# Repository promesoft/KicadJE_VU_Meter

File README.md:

# KicadJE_VU_Meter
Faceplate for 35mm VU Meter

# Purpose

## Board 1
Adjustment:

Input Audio 
+/- 10V DC coupled

Output Audio  
+/- 10V DC coupled

# Status - Delivered
## Initial 
| Stage  | Detail | Status |
| ------------- | ------------- | ------------- |
| create material  | sch |OK
| | pcb |OK
| | gerber |OK
| production |  |  
|  | produced  |OK 
|  | delivered |OK
## Preliminary validation
| Test  | Detail | Status |
| ------------- | ------------- | ------------- |
| Initial Inspection | | ok |
| Mechanical Inspection | | 6,3mm jack on the small side |
| Initial Technical Test | Board 1 |  |
| Initial Product Test | Board1 |  |

## Secondary validation
| Test  | Detail | Status |
| ------------- | ------------- |------------- |
| Product Test | 1 | |
| Quality | 1 | |
| Long Term Product Test |  |  |
| Power Draw |  | 

## Errata
### Errata - 

## Issues and Notes
### 

# Pictures

# Schematic
## Sch 1

# Analysis
## Diag 1

## Prototype

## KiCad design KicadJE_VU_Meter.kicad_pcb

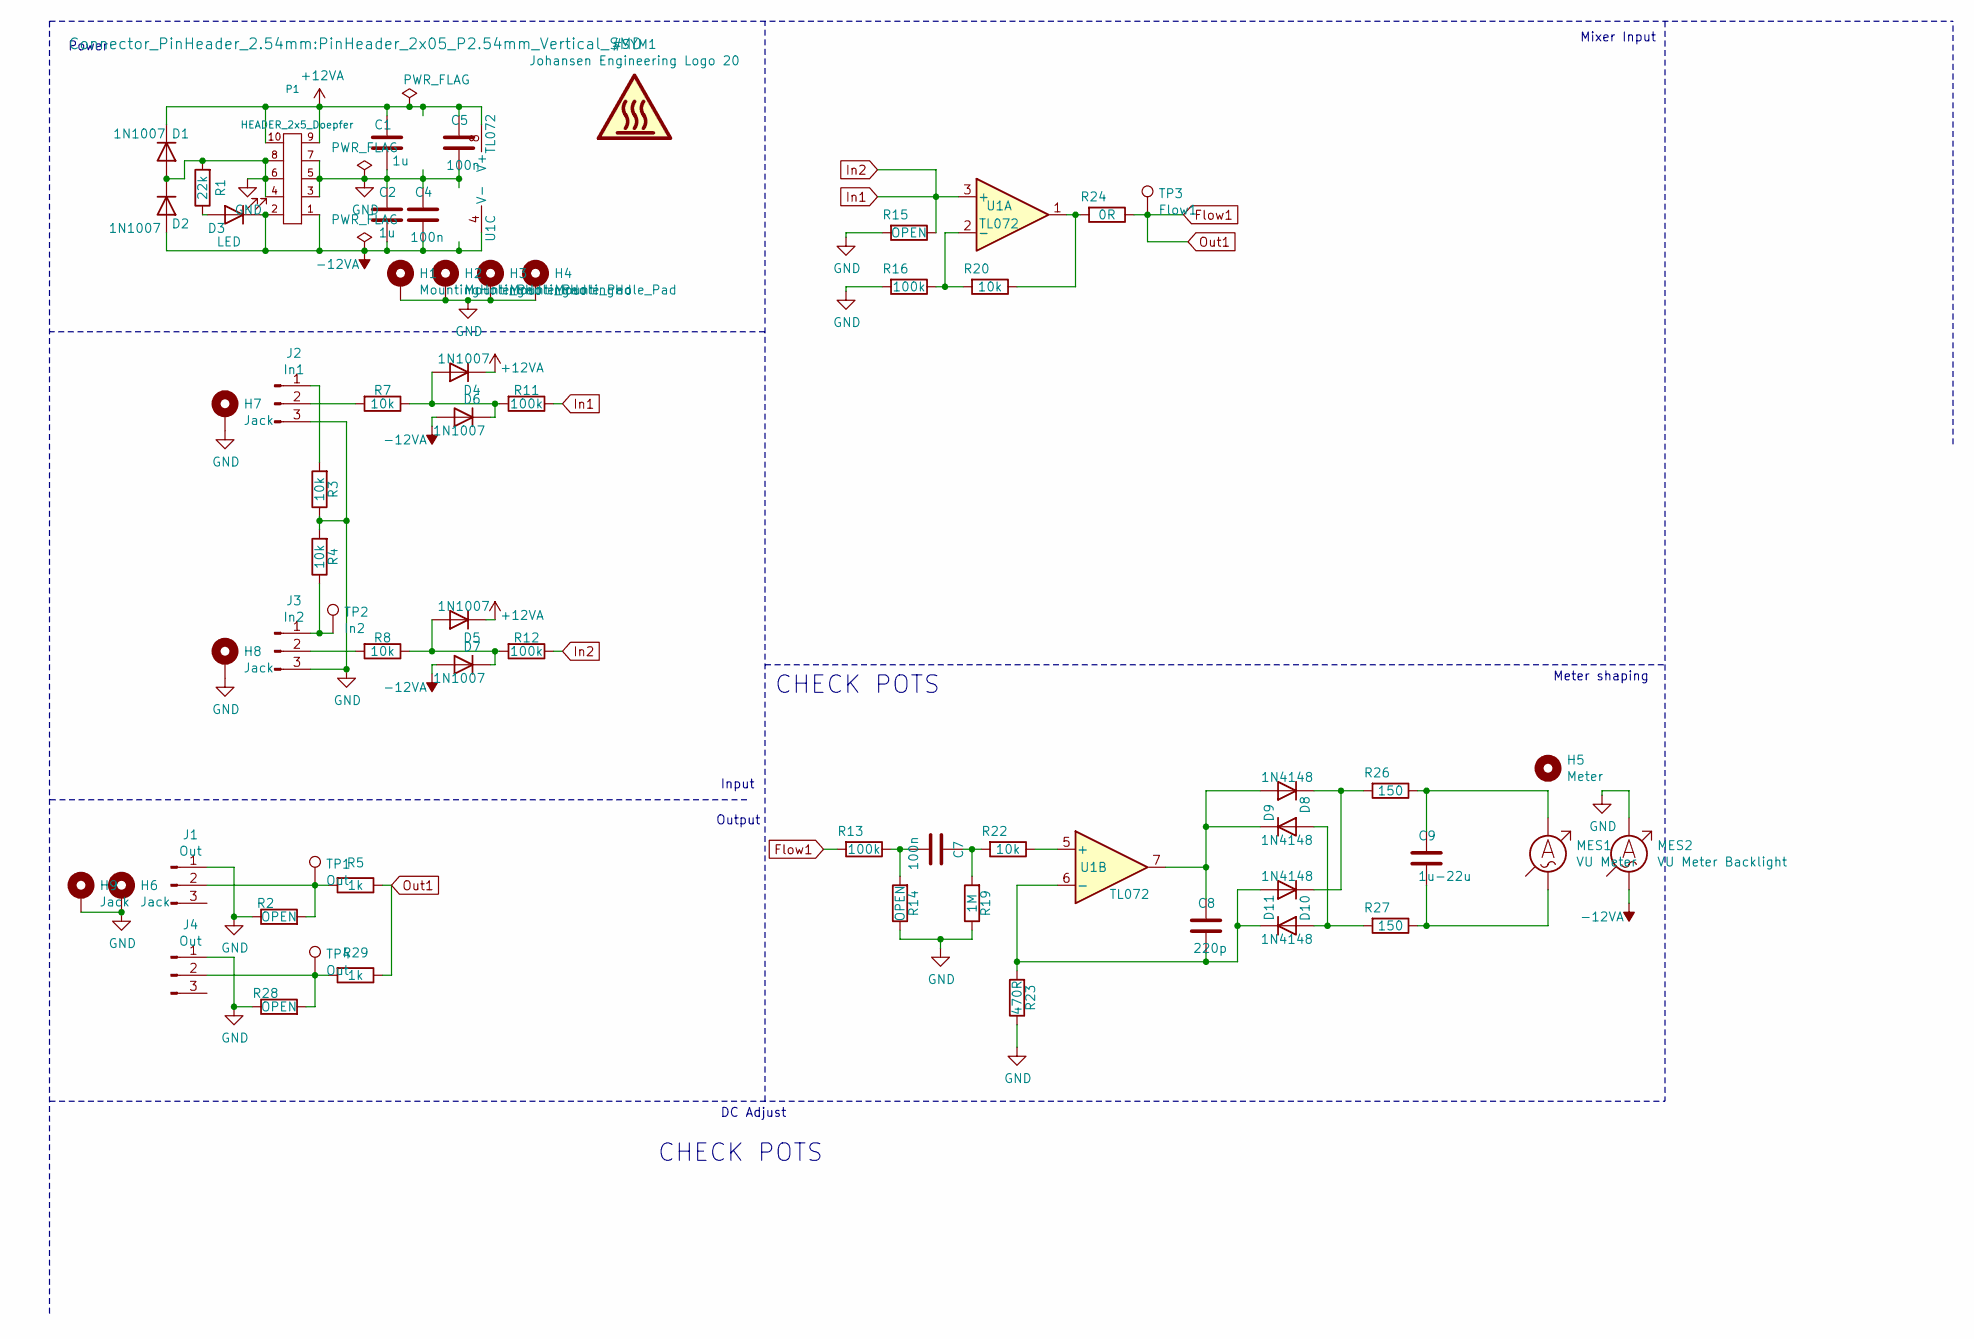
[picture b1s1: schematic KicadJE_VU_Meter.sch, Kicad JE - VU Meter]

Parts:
C1, C2: 1u; C_0805_2012Metric
C4, C5, C7: 100n; C_0805_2012Metric
C8: 220p; C_0805_2012Metric
C9: 1u-22u; C_1206_3216Metric
D1, D2, D4, D5, D6, D7: 1N1007; D_SOD-123
D3: LED; LED_0805_2012Metric_Pad1.15x1.40mm_HandSolder
D8, D9, D10, D11: 1N4148; D_MiniMELF
H1, H2, H3, H4: MountingHole_Pad; MountingHole_Eurorack3
H5: Meter; VU_Meter_Hole
H6: Jack; Jack_6m3
H7, H8, H9: Jack; Jack_3m5
J1, J4: Out; PinHeader_1x03_P2.54mm_Vertical_SMD_Pin1Right
J2: In1; PinHeader_1x03_P2.54mm_Vertical_SMD_Pin1Right
J3: In2; PinHeader_1x03_P2.54mm_Vertical_SMD_Pin1Right
MES1: VU Meter; PinHeader_1x02_P2.54mm_Vertical_SMD_Pin1Right
MES2: VU Meter Backlight; PinHeader_1x02_P2.54mm_Vertical_SMD_Pin1Right
P1: HEADER_2x5_Doepfer; PinHeader_2x05_P2.54mm_Vertical_SMD
R1: 22k; R_0805_2012Metric_Pad1.20x1.40mm_HandSolder
R2, R14, R15, R28: OPEN; R_0805_2012Metric_Pad1.20x1.40mm_HandSolder
R3, R4, R7, R8, R20, R22: 10k; R_0805_2012Metric_Pad1.20x1.40mm_HandSolder
R5, R29: 1k; R_0805_2012Metric_Pad1.20x1.40mm_HandSolder
R11, R12, R13, R16: 100k; R_0805_2012Metric_Pad1.20x1.40mm_HandSolder
R19: 1M; R_0805_2012Metric_Pad1.20x1.40mm_HandSolder
R23: 470R; R_0805_2012Metric_Pad1.20x1.40mm_HandSolder
R24: 0R; R_0805_2012Metric_Pad1.20x1.40mm_HandSolder
R26, R27: 150; R_0805_2012Metric_Pad1.20x1.40mm_HandSolder
TP1, TP4: Out; TestPoint_Pad_D2.0mm
TP2: In2; TestPoint_Pad_D2.0mm
TP3: Flow1; TestPoint_Pad_D2.0mm
U1: TL072; SO-8_5.3x6.2mm_P1.27mm

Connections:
+12VA: C1.1, C5.1, D1.1 (K), D4.1 (K), D5.1 (K), P1.9 (+12), P1.10 (+12), U1.8 (V+)
-12VA: C2.2, C4.2, D2.2 (A), D3.1 (K), D6.2 (A), D7.2 (A), MES2.1, P1.1 (-12), P1.2 (-12), U1.4 (V-)
Flow1: R5.1, R13.2, R24.1, R29.1, TP3.1
GND: C1.2, C2.1, C4.1, C5.2, D1.2 (A), D2.1 (K), H1.1, H2.1, H3.1, H4.1, H6.1, H7.1, H8.1, H9.1, J1.1, J2.3, J3.3, J4.1, MES2.2, P1.3 (GND), P1.4 (GND), P1.5 (GND), P1.6 (GND), P1.7 (GND), P1.8 (GND), R1.2, R2.1, R3.1, R4.2, R14.1, R15.2, R16.2, R19.1, R23.1, R28.1
In1: R11.1, R12.1, R15.1, U1.3 (+)
unnamed: C7.1, R19.2, R22.2
unnamed: C7.2, R13.1, R14.2
unnamed: C8.1, D8.2 (A), D9.1 (K), U1.7
unnamed: C8.2, D10.2 (A), D11.1 (K), R23.2, U1.6 (-)
unnamed: C9.1, MES1.2, R26.1
unnamed: C9.2, MES1.1, R27.1
unnamed: D3.2 (A), R1.1
unnamed: D4.2 (A), D6.1 (K), R7.1, R11.2
unnamed: D5.2 (A), D7.1 (K), R8.1, R12.2
unnamed: D8.1 (K), D10.1 (K), R26.2
unnamed: D9.2 (A), D11.2 (A), R27.2
unnamed: J1.2, R2.2, R5.2, TP1.1
unnamed: J2.1, R3.2
unnamed: J2.2, R7.2
unnamed: J3.1, R4.1, TP2.1
unnamed: J3.2, R8.2
unnamed: J4.2, R28.2, R29.2, TP4.1
unnamed: R16.1, R20.2, U1.2 (-)
unnamed: R20.1, R24.2, U1.1
unnamed: R22.1, U1.5 (+)

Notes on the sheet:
DC Adjust
Power
Input
Output
CHECK POTS
Mixer Input
Meter shaping

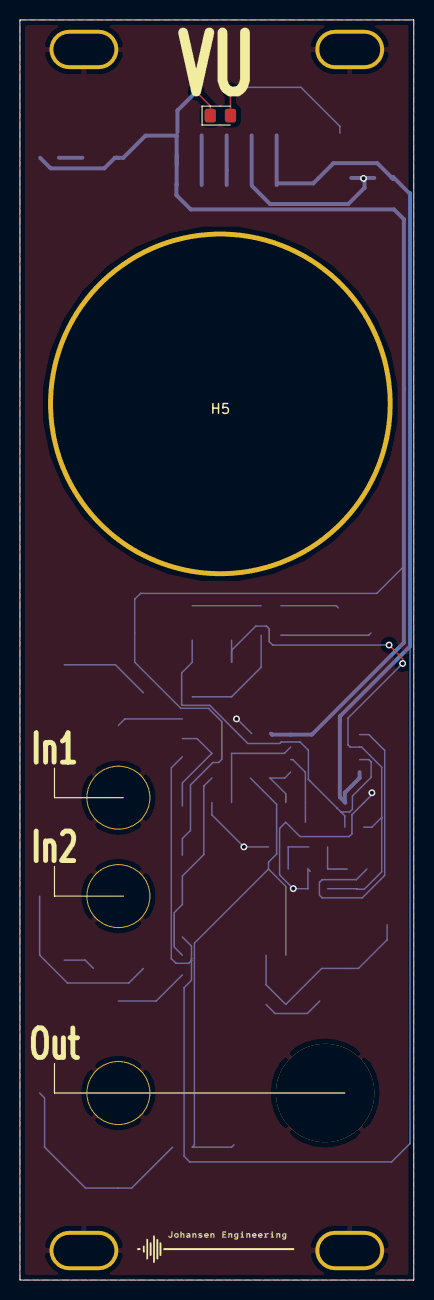
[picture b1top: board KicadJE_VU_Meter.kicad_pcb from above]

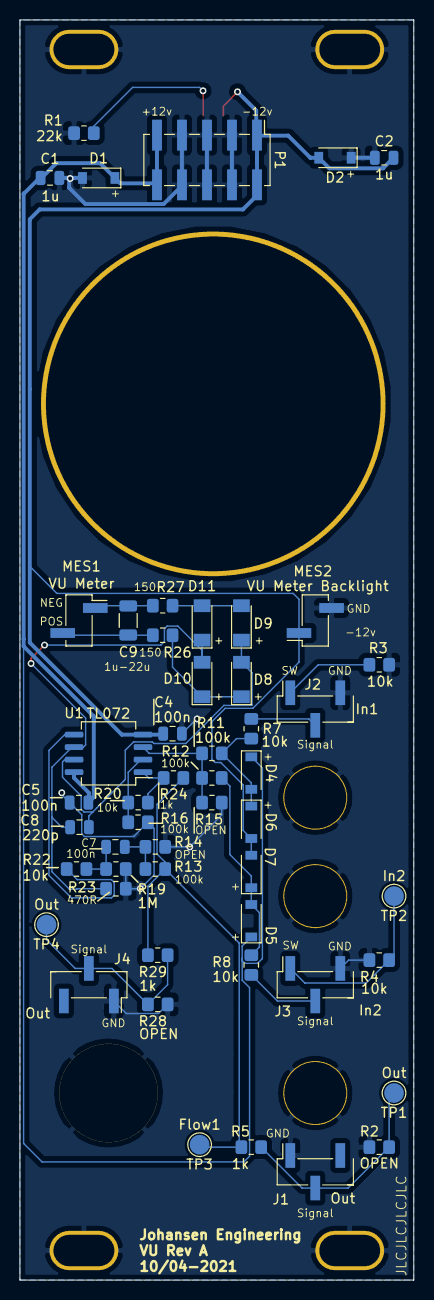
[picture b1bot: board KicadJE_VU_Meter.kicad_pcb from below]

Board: 2 copper layers, 40.0 x 128.0 mm, 61 parts (53 on the bottom side), 25 nets.

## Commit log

2021-04-10 Diagram tested on breadboard
2021-04-10 Footprint updates
2021-04-10 Update KicadJE_VU_Meter.sch
    update resistors and capacitors footprints
2021-04-10 Footprint and faceplate cleanup
2021-04-10 Removed second op amp
    save space
2021-04-10 Update KicadJE_VU_Meter.kicad_pcb
    Routed
2021-04-11 Reposition VU meter
    To make sure there is room for the power conn.
    2mm available for jacks
2021-04-11 Adjusting labels
2021-04-11 Faceplate cleanup
2021-04-11 Gerber
